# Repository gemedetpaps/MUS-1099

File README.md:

# MUS-1099
ISA sound card based on the SAA1099 sound generator

This card is based on the work by Sergey and Tronix of the Vintage Computer Federation forums and is an attempt at 
creating a working clone of the Creative CMS / Game Blaster ISA cards.

More information can be found at http://www.vcfed.org/forum/showthread.php?59846-Creative-Music-System-Game-Blaster-clone

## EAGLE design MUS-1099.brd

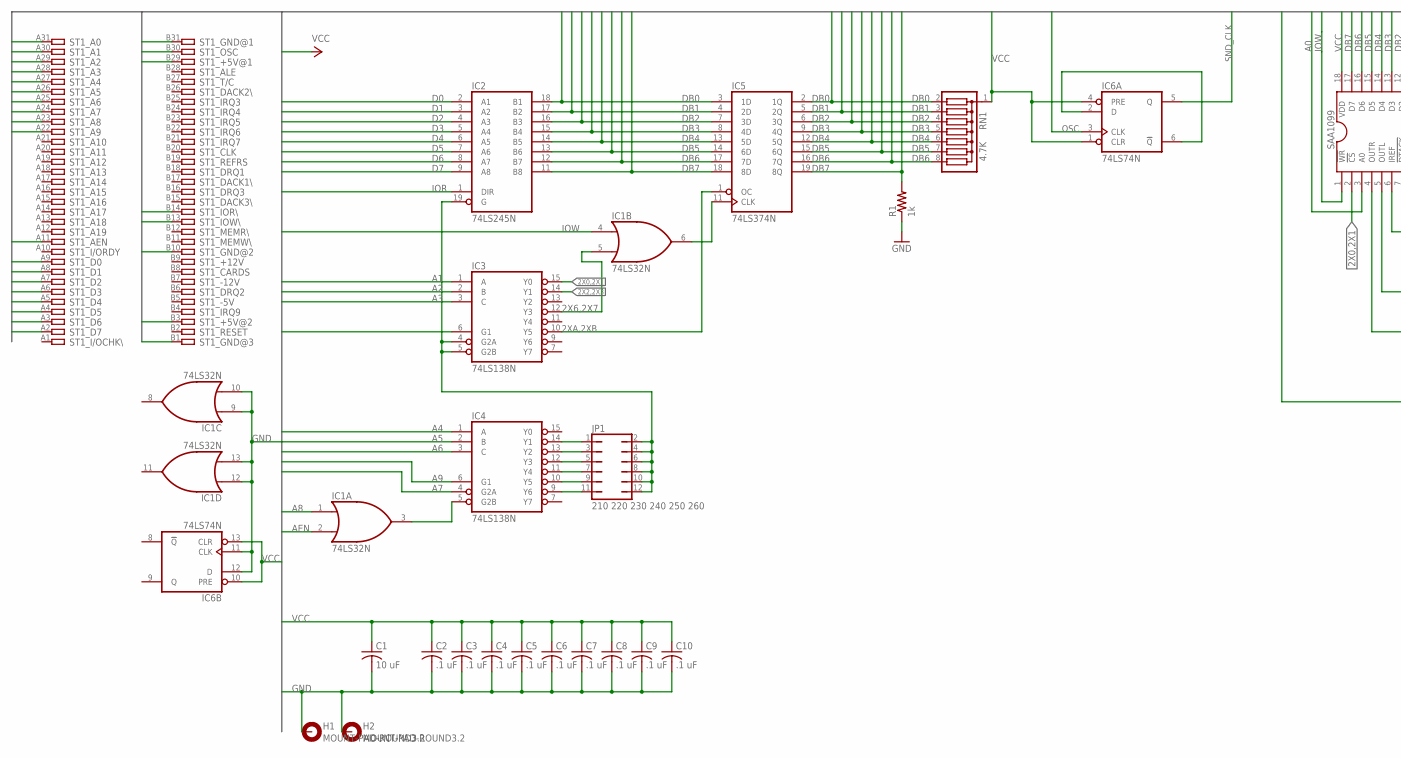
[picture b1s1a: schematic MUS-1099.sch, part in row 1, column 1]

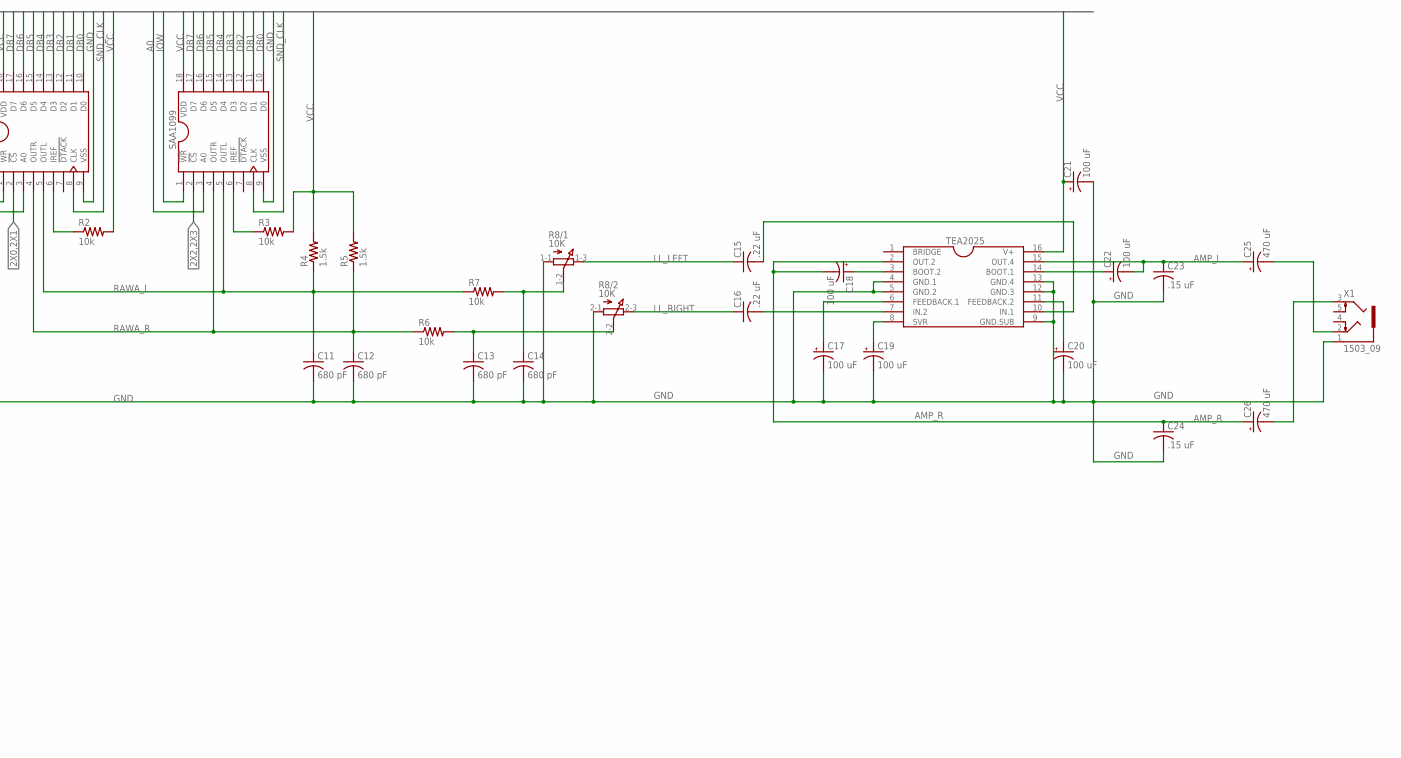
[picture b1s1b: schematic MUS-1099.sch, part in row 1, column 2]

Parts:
C1: 10 uF; C025-025X050
C2, C3, C4, C5, C6, C7, C8, C9, C10: .1 uF; C025-025X050
C11, C12, C13, C14: 680 pF; C025-025X050
C15, C16: .22 uF; C025-025X050
C17, C18, C19, C20, C21, C22: 100 uF; E5-10,5
C23, C24: .15 uF; C025-025X050
C25, C26: 470 uF; E5-10,5
H1, H2: MOUNT-PAD-ROUND3.2; 3,2-PAD
IC1: 74LS32N; DIL14
IC2: 74LS245N; DIL20
IC3, IC4: 74LS138N; DIL16
IC5: 74LS374N; DIL20
IC6: 74LS74N; DIL14
IC7, IC8: SAA1099; DIL18
IC9: TEA2025; DIL16
JP1: 210 220 230 240 250 260; JP6Q
R1: 1k; 0207/10
R2, R3, R6, R7: 10k; 0207/10
R4, R5: 1.5k; 0207/10
R8: 10K; 3RP/1610G
RN1: 4.7K; SIL8
ST1: 8 bit ISA; IBM8BIT
X1: 1503_09

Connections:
2X0,2X1: IC3.15 (Y0), IC7.2 (!CS!)
2X2,2X3: IC3.14 (Y1), IC8.2 (!CS!)
2X6,2X7: IC1.5 (I1), IC3.12 (Y3)
2XA,2XB: IC3.10 (Y5), IC5.1 (OC)
A0: IC7.3 (A0), IC8.3 (A0), ST1.A31
A1: IC3.1 (A), ST1.A30
A2: IC3.2 (B), ST1.A29
A3: IC3.3 (C), ST1.A28
A4: IC4.1 (A), ST1.A27
A5: IC4.2 (B), ST1.A26
A6: IC4.3 (C), ST1.A25
A7: IC4.4 (G2A), ST1.A24
A8: IC1.1 (I0), ST1.A23
A9: IC4.6 (G1), ST1.A22
AEN: IC1.2 (I1), ST1.A11
AMP_L: C22.-, C23.1, C25.+, IC9.15 (OUT.4)
AMP_R: C18.-, C24.1, C26.+, IC9.2 (OUT.2)
D0: IC2.2 (A1), ST1.A9
D1: IC2.3 (A2), ST1.A8
D2: IC2.4 (A3), ST1.A7
D3: IC2.5 (A4), ST1.A6
D4: IC2.6 (A5), ST1.A5
D5: IC2.7 (A6), ST1.A4
D6: IC2.8 (A7), ST1.A3
D7: IC2.9 (A8), ST1.A2
DB0: IC2.18 (B1), IC5.2 (1Q), IC5.3 (1D), IC7.10 (D0), IC8.10 (D0), RN1.2
DB1: IC2.17 (B2), IC5.4 (2D), IC5.5 (2Q), IC7.11 (D1), IC8.11 (D1), RN1.3
DB2: IC2.16 (B3), IC5.6 (3Q), IC5.7 (3D), IC7.12 (D2), IC8.12 (D2), RN1.4
DB3: IC2.15 (B4), IC5.8 (4D), IC5.9 (4Q), IC7.13 (D3), IC8.13 (D3), RN1.5
DB4: IC2.14 (B5), IC5.12 (5Q), IC5.13 (5D), IC7.14 (D4), IC8.14 (D4), RN1.6
DB5: IC2.13 (B6), IC5.14 (6D), IC5.15 (6Q), IC7.15 (D5), IC8.15 (D5), RN1.7
DB6: IC2.12 (B7), IC5.16 (7Q), IC5.17 (7D), IC7.16 (D6), IC8.16 (D6), RN1.8
DB7: IC2.11 (B8), IC5.18 (8D), IC5.19 (8Q), IC7.17 (D7), IC8.17 (D7), R1.2
GND: C1.2, C2.2, C3.2, C4.2, C5.2, C6.2, C7.2, C8.2, C9.2, C10.2, C11.2, C12.2, C13.2, C14.2, C17.-, C19.-, C20.-, C21.-, C23.2, C24.2, H1.B3,2, H2.B3,2, IC1.7 (GND), IC1.9 (I0), IC1.10 (I1), IC1.12 (I0), IC1.13 (I1), IC2.10 (GND), IC3.8 (GND), IC4.8 (GND), IC5.10 (GND), IC6.7 (GND), IC6.11 (CLK), IC6.12 (D), IC7.9 (VSS), IC8.9 (VSS), IC9.4 (GND.1), IC9.5 (GND.2), IC9.9 (GND.SUB), IC9.12 (GND.3), IC9.13 (GND.4), R1.1, R8.1-1 (A), R8.2-1 (A), ST1.B1, ST1.B10, ST1.B31, X1.1
IOR: IC2.1 (DIR), ST1.B14
IOW: IC1.4 (I0), IC7.1 (!WR!), IC8.1 (!WR!), ST1.B13
LL_LEFT: C15.1, R8.1-3 (E)
LL_RIGHT: C16.1, R8.2-3 (E)
N210: IC4.14 (Y1), JP1.1
N220: IC4.13 (Y2), JP1.3
N230: IC4.12 (Y3), JP1.5
N240: IC4.11 (Y4), JP1.7
N250: IC4.10 (Y5), JP1.9
N260: IC4.9 (Y6), JP1.11
unnamed: IC1.3 (O), IC4.5 (G2B)
unnamed: IC2.19 (G), IC3.4 (G2A), IC3.5 (G2B), JP1.2, JP1.4, JP1.6, JP1.8, JP1.10, JP1.12
unnamed: IC1.6 (O), IC5.11 (CLK)
unnamed: IC6.2 (D), IC6.6 (!Q)
unnamed: C13.1, R6.2, R8.2-2 (S)
unnamed: C14.1, R7.2, R8.1-2 (S)
unnamed: IC7.6 (IREF), R2.1
unnamed: IC8.6 (IREF), R3.1
unnamed: C16.2, IC9.7 (IN.2)
unnamed: C15.2, IC9.10 (IN.1)
unnamed: C17.+, IC9.6 (FEEDBACK.1)
unnamed: C20.+, IC9.11 (FEEDBACK.2)
unnamed: C25.-, X1.2
unnamed: C26.-, X1.3
unnamed: C19.+, IC9.8 (SVR)
unnamed: C22.+, IC9.14 (BOOT.1)
unnamed: C18.+, IC9.3 (BOOT.2)
OSC: IC6.3 (CLK), ST1.B30
RAWA_L: C11.1, IC7.5 (OUTL), IC8.5 (OUTL), R4.1, R7.1
RAWA_R: C12.1, IC7.4 (OUTR), IC8.4 (OUTR), R5.1, R6.1
SND_CLK: IC6.5 (Q), IC7.8 (CLK), IC8.8 (CLK)
VCC: C1.1, C2.1, C3.1, C4.1, C5.1, C6.1, C7.1, C8.1, C9.1, C10.1, C21.+, IC1.14 (VCC), IC2.20 (VCC), IC3.6 (G1), IC3.16 (VCC), IC4.16 (VCC), IC5.20 (VCC), IC6.1 (CLR), IC6.4 (PRE), IC6.10 (PRE), IC6.13 (CLR), IC6.14 (VCC), IC7.18 (VDD), IC8.18 (VDD), IC9.16 (V+), R2.2, R3.2, R4.2, R5.2, RN1.1, ST1.B3, ST1.B29

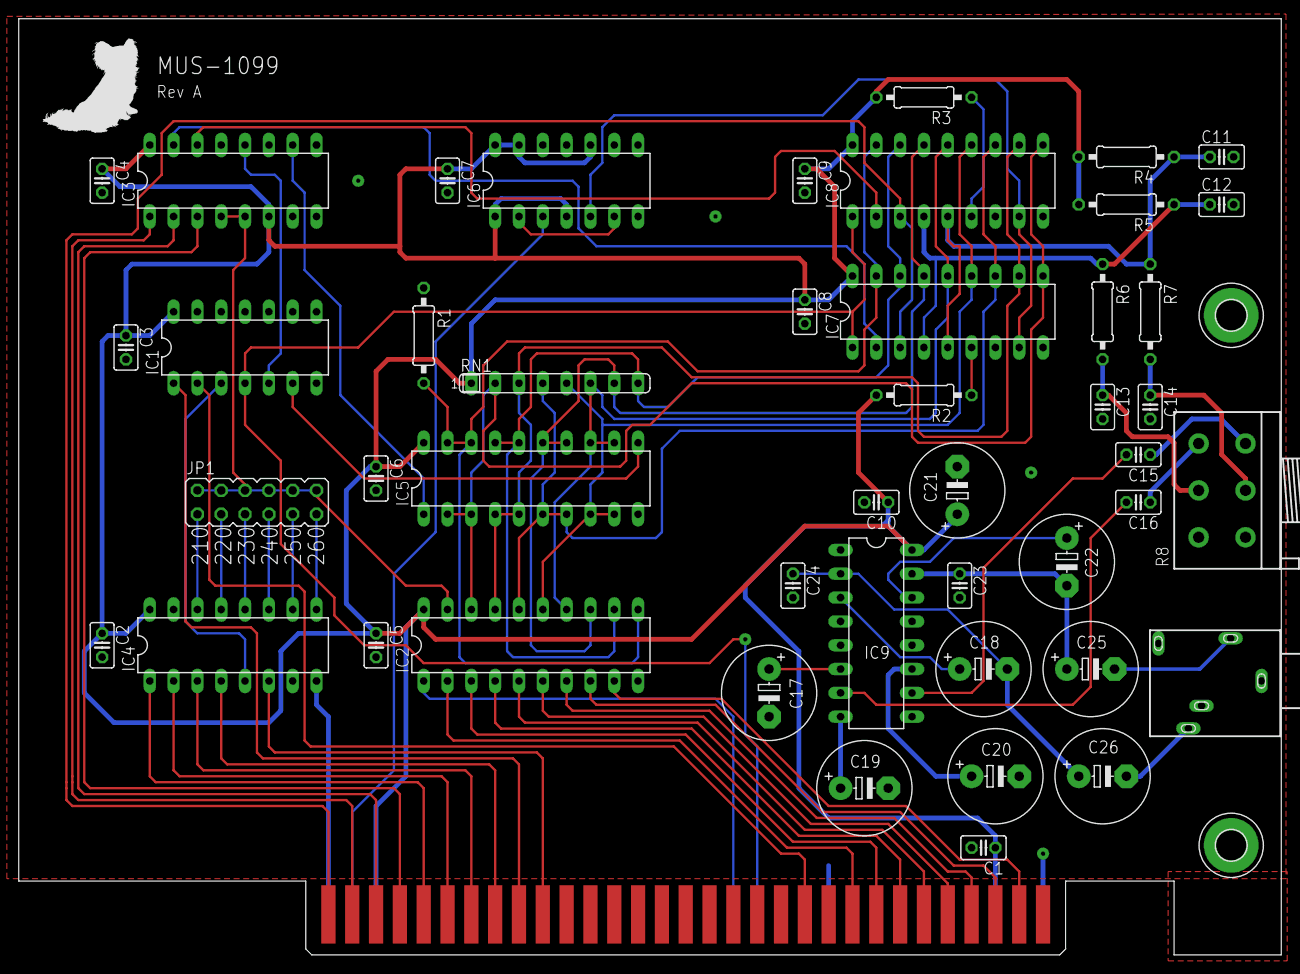
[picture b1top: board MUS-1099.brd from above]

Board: 2 copper layers, 134.6 x 99.8 mm, 50 parts (0 on the bottom side), 66 nets.

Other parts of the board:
U$1: LOGO

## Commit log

2017-09-24 Initial Commit of REV A
2017-09-24 Parts List
